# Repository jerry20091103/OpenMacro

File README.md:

# OpenMacro
A extensible macro device and password manager built with Arduino.

## About this repository

This repository contains three subprojects:
* **OpenMacro-Arduino:** A macropad program designed to be run on an Arduino Micro board.
* **OpenMacro-GUI:** A Qt application that can be used to configure an OpenMacro device. You will need the Arduino USB driver to detect the Arduino board.
* **OpenMacro-PCB:** A KiCad project that contains the layouts of a complete OpenMacro device.

Note that the OpenMacro-GUI project has a dependency to the OpenMacro-Arduino project's `Keycodes.h` and `MacroConfig.h`.

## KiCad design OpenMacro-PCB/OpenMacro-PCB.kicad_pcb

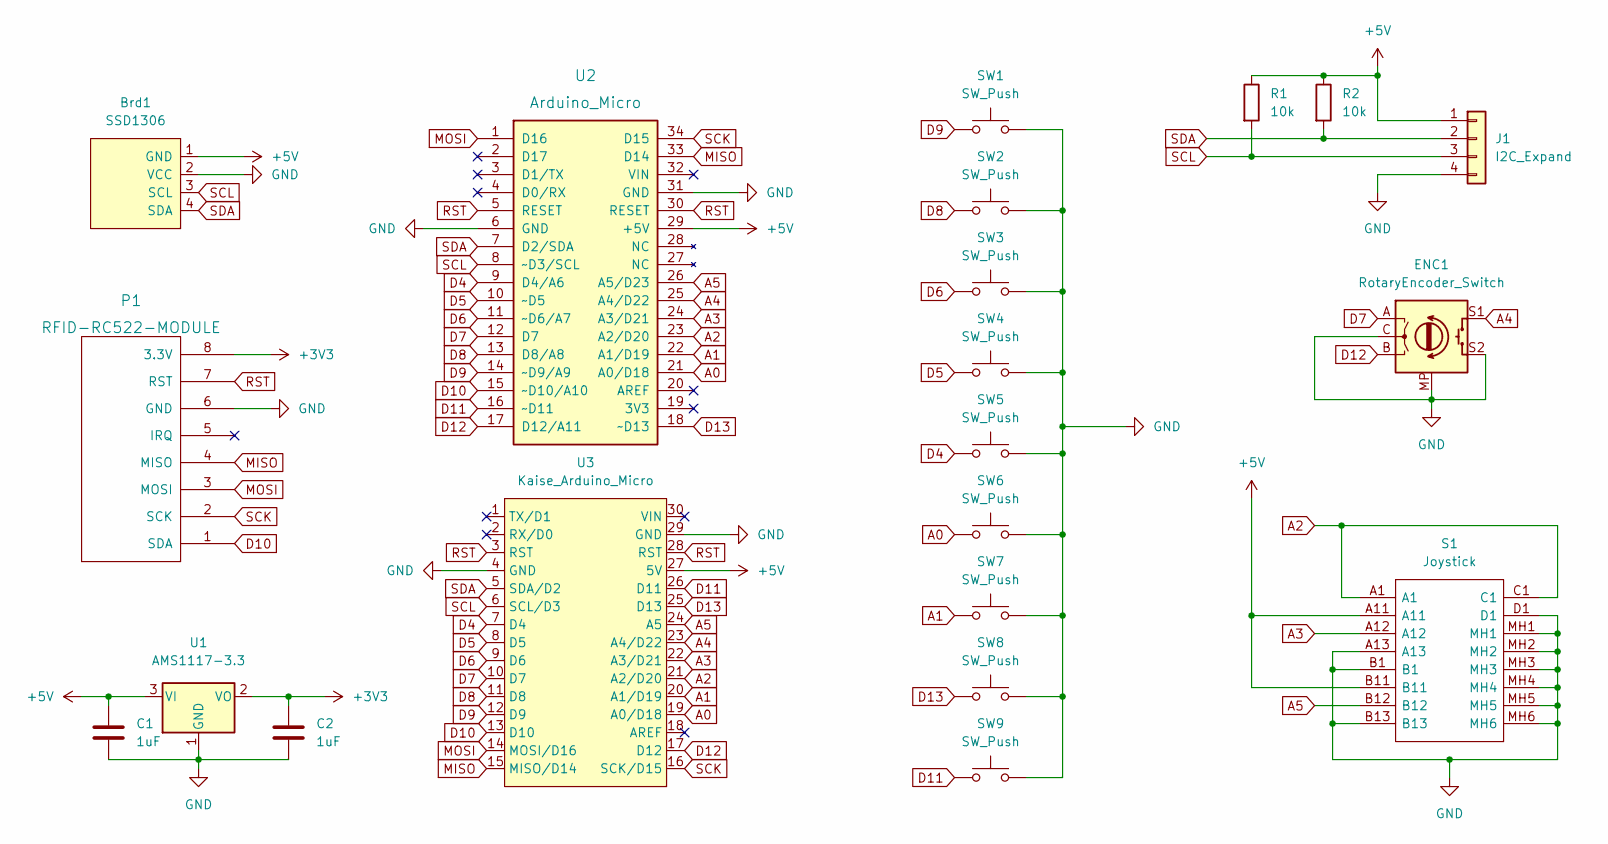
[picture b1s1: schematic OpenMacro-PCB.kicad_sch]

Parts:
Brd1: SSD1306; 128x64OLED
C1, C2: 1uF; C_1206_3216Metric_Pad1.33x1.80mm_HandSolder
ENC1: RotaryEncoder_Switch; RotaryEncoder_Alps_EC11E-Switch_Vertical_H20mm_CircularMoun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
J1: I2C_Expand; PinSocket_1x04_P2.54mm_Horizontal
P1: RFID-RC522-MODULE; RC-522-RFID
R1, R2: 10k; R_1206_3216Metric_Pad1.30x1.75mm_HandSolder
S1: Joystick; RKJXV122400R; Mouser Part Number 688-RKJXV122400R
SW1, SW2, SW3, SW4, SW5, SW6, SW7, SW8, SW9: SW_Push; MX-Alps-Choc-1U-NoLED
U1: AMS1117-3.3; SOT-223-3_TabPin2
U2: Arduino_Micro
U3: Kaise_Arduino_Micro

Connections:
+3V3: C2.1, P1.8 (3.3V), U1.2 (VO)
+5V: Brd1.1 (GND), C1.1, J1.1, R1.1, R2.1, S1.A11, S1.B11, U1.3 (VI), U2.29 (+5V), U3.27 (5V)
A0: SW6.1, U2.21 (A0/D18), U3.19 (A0/D18)
A1: SW7.1, U2.22 (A1/D19), U3.20 (A1/D19)
A2: S1.A1, S1.C1, U2.23 (A2/D20), U3.21 (A2/D20)
A3: S1.A12, U2.24 (A3/D21), U3.22 (A3/D21)
A4: ENC1.S1, U2.25 (A4/D22), U3.23 (A4/D22)
A5: S1.B12, U2.26 (A5/D23), U3.24 (A5)
D4: SW5.1, U2.9 (D4/A6), U3.7 (D4)
D5: SW4.1, U2.10 (~D5), U3.8 (D5)
D6: SW3.1, U2.11 (~D6/A7), U3.9 (D6)
D7: ENC1.A, U2.12 (D7), U3.10 (D7)
D8: SW2.1, U2.13 (D8/A8), U3.11 (D8)
D9: SW1.1, U2.14 (~D9/A9), U3.12 (D9)
D10: P1.1 (SDA), U2.15 (~D10/A10), U3.13 (D10)
D11: SW9.1, U2.16 (~D11), U3.26 (D11)
D12: ENC1.B, U2.17 (D12/A11), U3.17 (D12)
D13: SW8.1, U2.18 (~D13), U3.25 (D13)
GND: Brd1.2 (VCC), C1.2, C2.2, ENC1.C, ENC1.MP, ENC1.S2, J1.4, P1.6 (GND), S1.A13, S1.B1, S1.B13, S1.D1, S1.MH1, S1.MH2, S1.MH3, S1.MH4, S1.MH5, S1.MH6, SW1.2, SW2.2, SW3.2, SW4.2, SW5.2, SW6.2, SW7.2, SW8.2, SW9.2, U1.1 (GND), U2.6 (GND), U2.31 (GND), U3.4 (GND), U3.29 (GND)
MISO: P1.4 (MISO), U2.33 (D14), U3.15 (MISO/D14)
MOSI: P1.3 (MOSI), U2.1 (D16), U3.14 (MOSI/D16)
RST: P1.7 (RST), U2.5 (RESET), U2.30 (RESET), U3.3 (RST), U3.28 (RST)
SCK: P1.2 (SCK), U2.34 (D15), U3.16 (SCK/D15)
SCL: Brd1.3 (SCL), J1.3, R1.2, U2.8 (~D3/SCL), U3.6 (SCL/D3)
SDA: Brd1.4 (SDA), J1.2, R2.2, U2.7 (D2/SDA), U3.5 (SDA/D2)

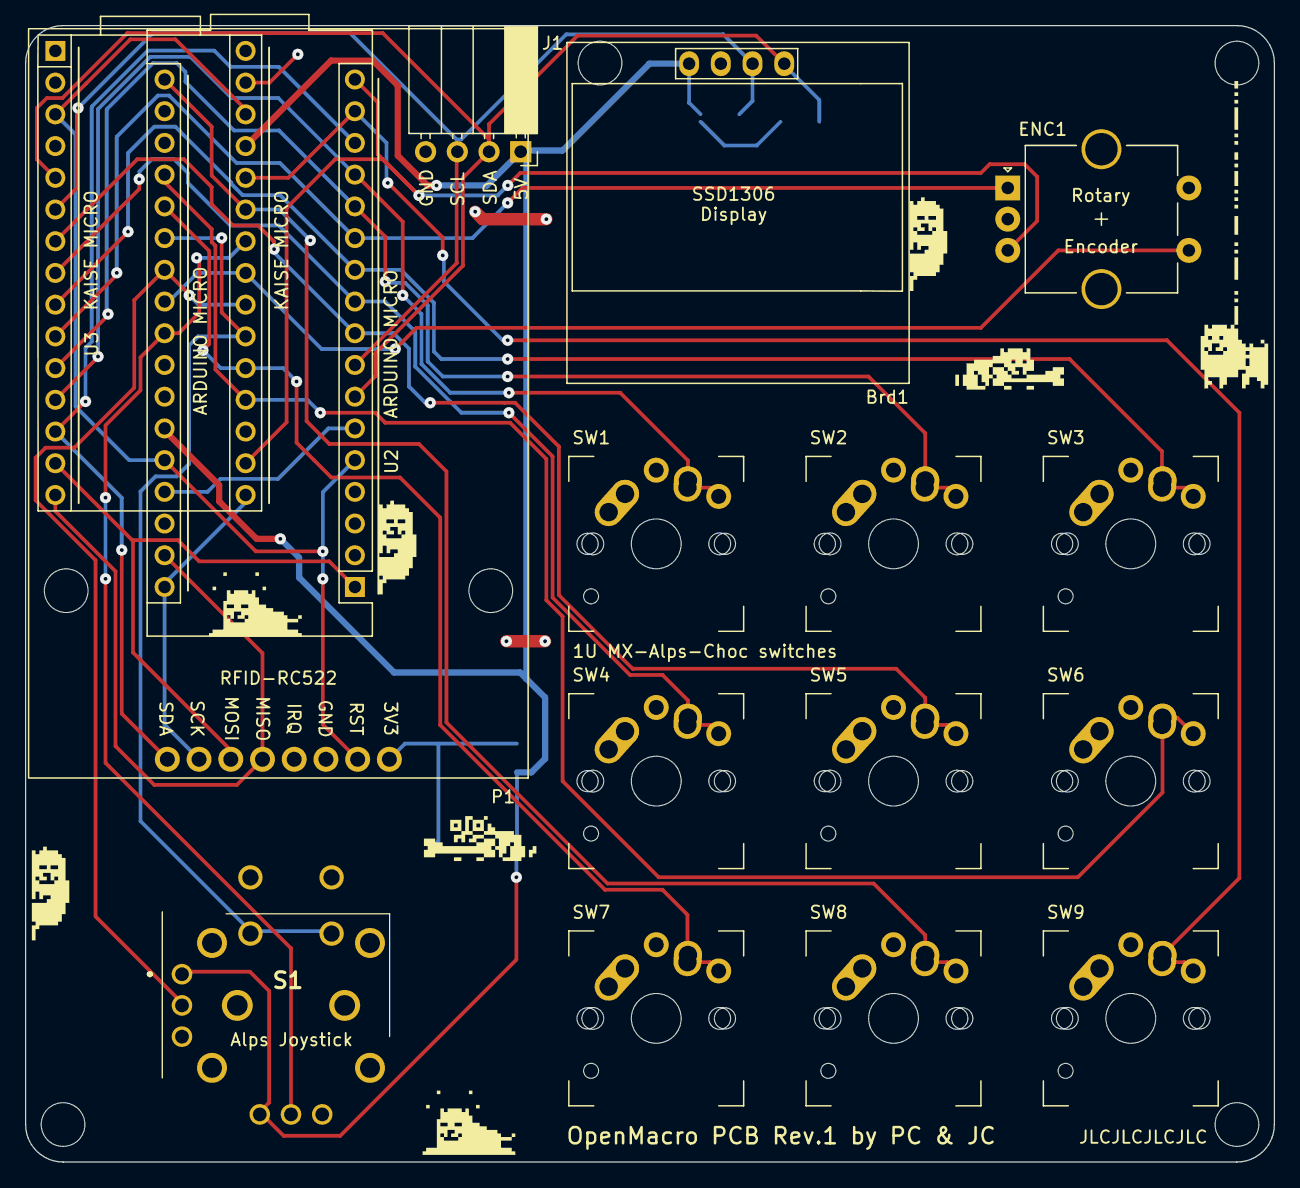
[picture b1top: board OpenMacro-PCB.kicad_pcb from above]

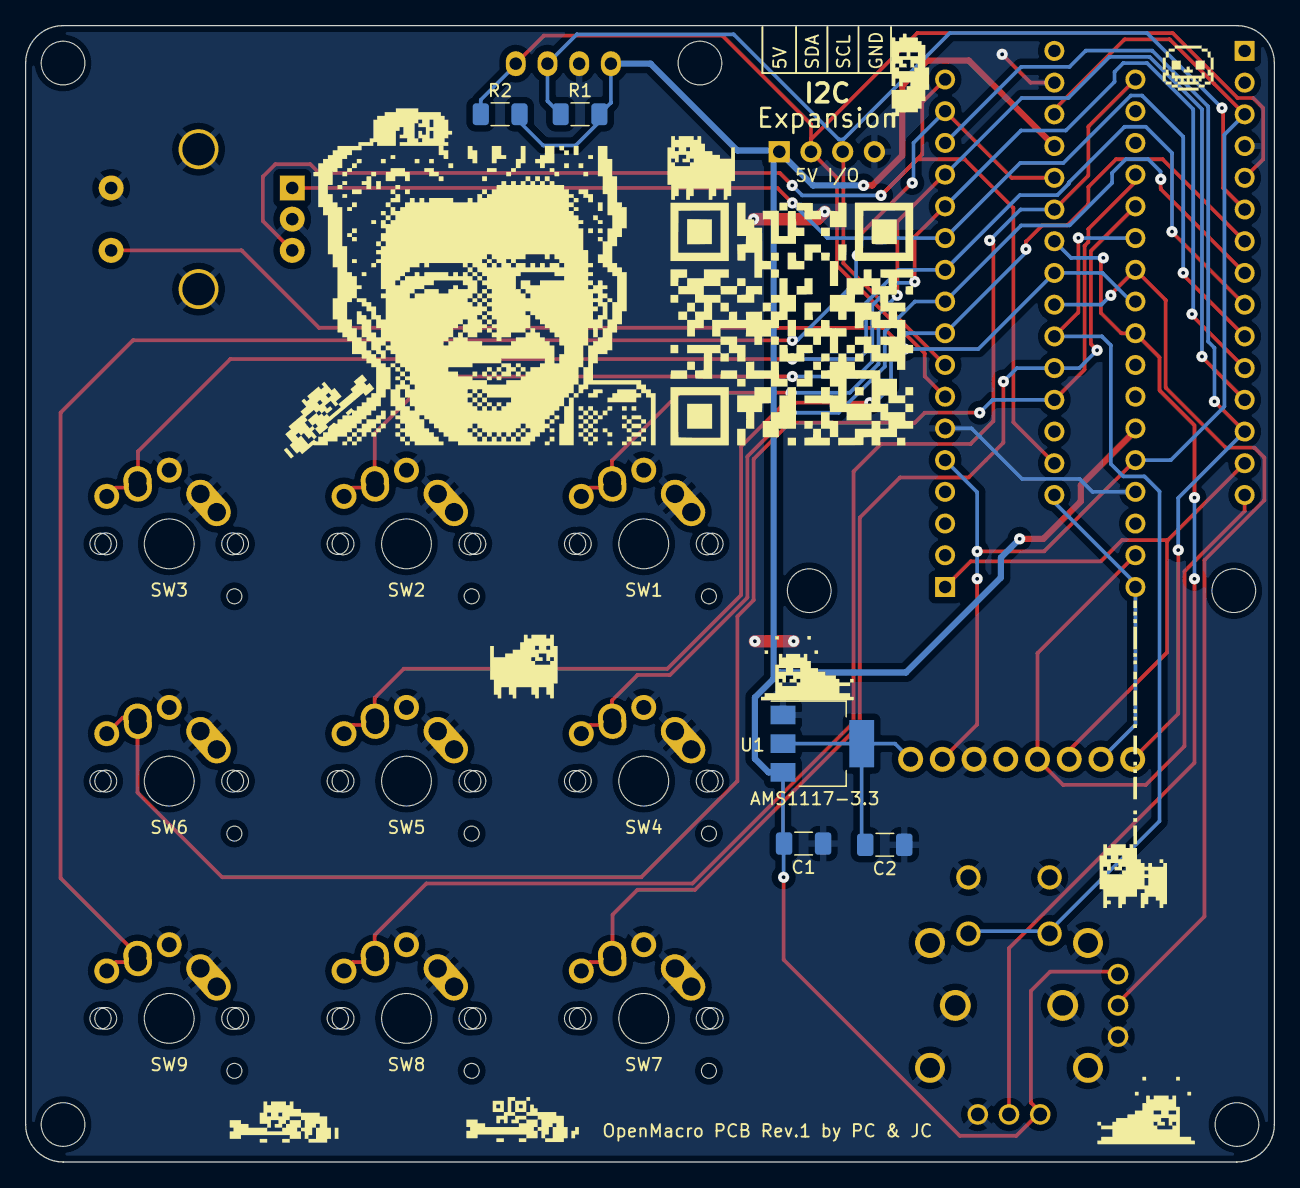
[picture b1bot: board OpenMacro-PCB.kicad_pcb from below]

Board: 2 copper layers, 100.0 x 91.0 mm, 21 parts (5 on the bottom side), 25 nets.

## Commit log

2022-04-30 Add Parts List.
2022-05-01 Added Qt project
2022-05-01 Added missing explanation for gitignore
2022-05-13 Set up serial debugging.
2022-05-13 Add basic hardware testing code.
2022-05-13 Added baud rate
2022-05-13 Disable serial waiting.
2022-05-13 Serial read from qt works.
2022-05-13 Inlined baudRate for consistency
2022-05-13 Serial test now working.
2022-05-13 Resolved merge conflict
2022-05-14 Add key matrix, change display driver to text only
2022-05-21 CMake update
2022-05-21 Ignoring CMakeLists.txt.user
2022-05-21 Refactored GUI project structure and added Preset.
2022-05-21 Updated GUI's README.md
2022-05-21 Simplified UI design
2022-05-21 Renamed preset buttons.
2022-05-21 gitignore update for CMakeLists.txt.user, again
2022-05-21 Fixed debugmenu.h UI compile error.
2022-05-21 Addressed static const init issues
2022-05-21 Remove button matrix, change HID library.
2022-05-21 Add MacroConfig header.
2022-05-21 remove MacroConfig's depedency on arduino stuff.
2022-05-21 Add serialization API and keycode header.
2022-05-21 Presets menu progress
2022-05-21 Use stdint data types in MacroConfig.
2022-05-21 Preparation for displaying list of inputs
2022-05-21 Added InputList class and hooked up slots
2022-05-21 Update MacroConfig
2022-05-22 Use memcpy to serialize/deserialize config.
2022-05-22 Added missing include <stdint.h>
2022-05-22 Update MacroConfig again.
2022-05-22 data doesn't need to be pointer. It just stores offset.
2022-05-22 Added preset file i/o
2022-05-22 Added MAX_INPUTS define.
2022-05-23 Update MacroConfig.
2022-05-23 Update mouse and modifier in MacroConfig.
2022-05-23 Packed structs to minimize memory size.
2022-05-23 Finished setting up GUI layouts.
2022-05-24 Move passwords to a separate config struct.
2022-05-24 Finished macro functions for internal pins.
2022-05-25 Add Kicad PCB project files.
2022-05-30 Update kicad_sch.
2022-05-30 Update kicad_pcb.
2022-06-04 Added enum reflection for KeyboardKeycode
2022-06-05 Finished macro config GUI
2022-06-05 Added Connect to Device function.
2022-06-05 Fixed crash when switching inputs
2022-06-05 Port list fix
2022-06-05 Possible fix for segfault at size()
2022-06-05 Possible fix, again
2022-06-05 Better error messages
2022-06-05 Changed check order
2022-06-05 Added error string
2022-06-05 Made open/close more immediate
2022-06-05 Fix for preset dialog
2022-06-05 Possible fix
2022-06-05 Specified write size
2022-06-05 Reordered debug messages
2022-06-06 Use callbacks to close port instead
2022-06-06 Flush instead of waiting for byes written
2022-06-06 Unregistered timer during IO
2022-06-06 Set timerId to -1
2022-06-06 Use byte array instead
2022-06-06 Use std string -> char pointer instead
2022-06-06 Revert changes
2022-06-07 Added delay input spinbox
2022-06-07 Overflow bug fix
2022-06-09 Serial receive working. Macros still have problems
2022-06-10 Fixed some type mismatches
2022-06-10 Bugfix
2022-06-10 Use findText instead
2022-06-10 Specified input ranges for spinboxes
2022-06-10 Add permenant memory, change mouseMove data type.
2022-06-10 Fixed some UI issues
2022-06-10 Adjusted UI layout
2022-06-10 Adjusted UI layout again
2022-06-10 Added expander address GUI
2022-06-10 Wrap MacroConfig and PassowordConfig.
2022-06-10 Reduce code space.
2022-06-10 Expanded inputs now working.
2022-06-11 Fix force reset bug, add basic password support.
2022-06-12 Put running macros in tasks instead.
2022-06-12 Add joystick support, sqeeze a little more flash.
2022-06-12 Reduce more flash usage for AES.
2022-06-12 Switch to even smaller display driver; Add AES.
2022-06-13 Add AES128 with RFID UID as key.
2022-06-13 Add volume control support.
2022-06-14 Added password dialog
2022-06-14 Convert QChar string to C string
2022-06-14 Clear password after closing password dialog
2022-06-14 Password working, downloading does not work.
2022-06-14 Serial download working.
2022-06-14 After-download GUI fix
2022-06-14 Added download fail check
2022-06-14 Fix bug in download serial.
2022-06-14 Added mouse none
2022-06-14 Added QoL features
2022-06-14 Made prompt non-modal
2022-06-14 Add port filtering; reduce some flash usage.
2022-06-14 Fix portname bug.
2022-06-14 Use informative text instead
2022-06-14 Changed to async connections
2022-06-14 proper cleanup
2022-06-14 Removed unused variables
2022-06-14 Rewrite
2022-06-14 Fix again
2022-06-14 Fixes
2022-06-14 Add AES password encryption; fix memory issues
2022-06-15 Improve mouse move accuracy.
2022-06-15 Add long press to joystick button
2022-06-15 Fix bug in PCB.
2022-06-16 Update readme.md in OpenMacro-Arduino
2022-06-16 Update Readme.md in OpenMacro-PCB.
2022-06-16 Rename files.
2022-06-17 Corrected README.md
